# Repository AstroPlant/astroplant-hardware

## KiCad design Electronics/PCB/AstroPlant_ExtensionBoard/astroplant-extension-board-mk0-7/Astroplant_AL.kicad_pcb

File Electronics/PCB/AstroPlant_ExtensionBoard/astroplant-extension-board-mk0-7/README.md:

## Power supply configuration
You can select different configuration to supply the board, 
	On the 3.3V line: you can choose between power the board with the raspberry or with the onboard 3.3V generator
	On the 5V line you can choose to power the board through :
		Raspberry pi,
		Board 5V input,
		micro-USB
		
With the astroplant-kit you need 2 jumper :
		connect 3.3V with the onboard generator
		connect 5V to the Board 5V input,

## Boot-mode
To program the board you need the microcontroller to enter boot-mode, to do this power the board while pushing Boot button, or reset the board while pushing Boot button,
To leave Boot-mode, reset the board with the button, or switch the power Off and On without pushing on boot button

## Antenna 
Don't place R26 and C6 if you want to use the PCB antenna
or Don't place R25 to use the UFL connector with an antenna

## To manufacture the PCB you need these files:
  - gerber - track/component placement
  - .drl - drill placement 
  - .pos - component placement 
 These file are avaible in the /Outputs directory
 
The BOM is available in the main folder, as it is not part of the manufacturing files.

## If you want to generate new output files, follow these steps: 

First you'll need Kicad 7.0: https://www.kicad.org/download/ 
Then open the project by executing the .kicad_pro file, you will then be able to see the different elements of the project such as the schematic and the pcb,
If you want the gerber or drill map, open the pcb editor (.kicad_pcb) and go "File -> Fabrication output ->Gerbers/Drill/Component Placement/BOM".
For each file, select the output directory before generating

We'll use the general parameter for output files.
For Gerber, select layers: B_Cu,B_Mask,B_Paste,B_Silkscreen,F_Cu,F_Mask,F_Paste,F_Silkscreen,Edge_Cuts and User_Eco2
and leave the other options as they are.

Please note that if you have added new components, add an "MPN" (Manufacturer part number) field in the properties of 
these parts, which is the part identification number; this field will be used to generate the BOM. 

To generate the Bill of mateial (BOM) open the schematic editor 
and do: Tools -> Generate BOM and select bom_generator_astroplant in the folder bom, this is 
a python script that generates a BOM compatible with Eurocircuit.

Now that you have the output files you can have them manufactured and even have the components 
placed if you have the BOM, for example on Eurcocircuits.com

Here is a tutorial to do that : https://docs.google.com/document/d/1_ITujiSZbh2MQ0I3NJUg4zAOC5qoafzlOR5tIkIVDLY/edit?usp=sharing

# MK07

## Specs

* 5V Input
    * Power RPI
    * Power sensors actuators
* 24V Input
    * Mosfet Output
    * LEDs connector (not for the moment)
* 3x Buttons
    * GPIO5
    * GPIO6
    * GPIO7
* 2x 1-Wire lines (2 connectors)
    * GPIO17 Humidity
    * GPIO4 Water temp
* CO2 interface (Rx, Tx, 5V, GND)
* SPI interface (NRF24)
* I2C
    * 4x 3.3v
    * 2x 5V
* LEDs panel interface
    * GPIO21 Blue
    * GPIO20 Red
    * GPIO18 Far
* 3x mosfet output (5V or 24V) 2A
    * GPIO16 Fans
    * GPIO12 Pump
    * GPIO19 Spare
* Add LED
* Zigbee/Thread interface
* Analog to digital converter
	* 2x

GPIO13 is still not used

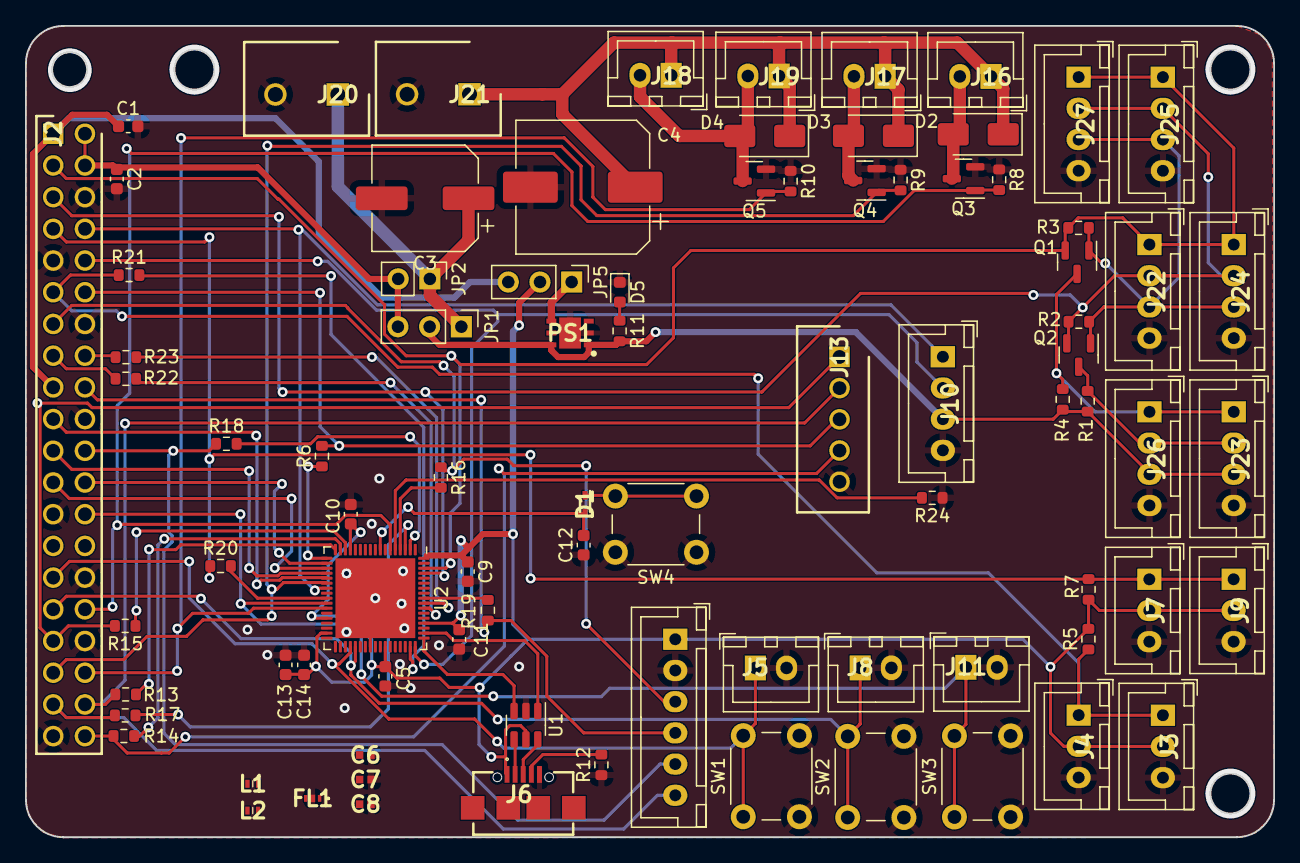
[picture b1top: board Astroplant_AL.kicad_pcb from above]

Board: 2 copper layers, 100.0 x 65.0 mm, 85 parts (0 on the bottom side), 64 nets.

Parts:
C1, C2, C5, C9, C10, C11, C12, C14: 100nF; C_0603_1608Metric
C3: 470uF; CP_Elec_8x6.9
C4: 470uF; CP_Elec_10x10.5
C6: GRM1555C1H1R2WA01D; CAPC1005X55N
C7: GRM1555C1HR30WA01D; CAPC1005X55N
C8: GRM1555C1HR80BA01D; CAPC1005X55N
C13: 100pF; C_0603_1608Metric
D1: BAT54KFILM; SODFL1608X70N
D2, D3, D4: S1A; D_SMA
D5: LED_Amber; LED_0603_1608Metric
FL1: LFB182G45CGFD436
J1: JST_XH_Relays; SHDR6W64P0X250_1X6_1740X575X700P
J2: 2x40 2.5mm Header; HDRV40W64P254X254_2X20_5080X508X869P
J3, J4, J7, J9: JST-XH_3; B3BXHALFSN
J5, J8, J11, J16, J17, J18, J19: JST_HX_2; SHDR2W64P0X250_1X2_740X575X700P
J6: 629105136821; MICRO-USB_2.0-SMT-TYPE-B_
J10: JST_XH_UART; B4BXHALFSN
J13: B5B-XH-A_LF__SN_; SHDR5W64P0X250_1X5_1490X575X700P
J20, J21: Conn_01x02; SHDR2W100P0X500_1X2_1000X750X990P
J22, J23, J24, J25, J26, J27: JST_XH_I2C; B4BXHALFSN
JP1, JP5: Jumper_3_Bridged12; PinHeader_1x03_P2.54mm_Vertical
JP2: Jumper_2_Bridged; PinHeader_1x02_P2.54mm_Vertical
L1: LQG15HS3N6S02D; LQG15WH0N7B02D
L2: LQG15HS2N7S02J; LQG15WH0N7B02D
PS1: LD39050PU33R; SON95P300X300X100-7N-D
Q1, Q2, Q3, Q4, Q5: IRLML6344TRPBF; SOT-23
R1, R2, R3, R4, R5, R7, R8, R9, R10, R12, R24: 10k; R_0603_1608Metric
R6, R13, R14, R15, R16, R17, R18, R19, R20, R21, R22, R23: 1k; R_0603_1608Metric
R11: 180; R_0603_1608Metric
SW1, SW2, SW3, SW4: SW_Push; SW_PUSH_6mm
U1: USBLC6-2SC6; SOT-23-6
U2: STM32WB55RGVx; QFN-68-1EP_8x8mm_P0.4mm_EP6.4x6.4mm

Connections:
3.3V_Generated: JP5.1 (A), PS1.4 (VOUT)
3.3V_RPi: C1.1, J2.1 (3V3), J2.17 (3V3), JP5.3 (B)
5V_IN: C3.1, J20.1, JP1.1 (A), JP2.1 (A)
5V_RPi: C2.1, J2.2 (5V), J2.4 (5V), JP1.3 (B), JP2.2 (B)
+3V3: C5.1, C9.1, C10.1, C11.1, C13.1, C14.1, J1.1 (DC+), J3.2 (PW), J4.2 (PW), J6.1, J7.2 (PW), J9.2 (PW), J22.3 (PW), J24.3 (PW), J25.3 (PW), J27.3 (PW), JP5.2 (C), Q1.1 (G), Q2.1 (G), R2.2, R3.2, R5.2, R7.2, U1.5 (VBUS), U2.14 (VDDA), U2.30 (VDD), U2.33 (VDDRF), U2.45 (VDD), U2.55 (VDDUSB), U2.68 (VDD)
+5V: J10.3 (PW), J23.3 (PW), J26.3 (PW), JP1.2 (C), PS1.1 (EN), PS1.6 (VIN), R1.2, R4.2, R11.2
+24V: C4.1, D2.1 (K), D3.1 (K), D4.1 (K), J16.1 (A), J17.1 (A), J18.1 (A), J19.1 (A), J21.1
CE0: J2.24 (~CE0/GPIO8), U2.19 (PA4)
GND: C1.2, C2.2, C3.2, C4.2, C5.2, C6.2, C7.2, C8.2, C9.2, C10.2, C11.2, C12.1, C13.2, C14.2, D5.1 (K), FL1.2 (GND), J1.2 (DC-), J2.6 (GND), J2.9 (GND), J2.14 (GND), J2.20 (GND), J2.25 (GND), J2.30 (GND), J2.34 (GND), J2.39 (GND), J3.3 (GND), J4.3 (GND), J5.2 (B), J6.5, J7.3 (GND), J8.2 (B), J9.3 (GND), J10.4 (GND), J11.2 (B), J13.5, J20.2, J21.2, J22.4 (GND), J23.4 (GND), J24.4 (GND), J25.4 (GND), J26.4 (GND), J27.4 (GND), PS1.2 (GND), PS1.7 (PAD), Q3.2 (S), Q4.2 (S), Q5.2 (S), R8.1, R9.1, R10.1, R12.1, R24.1, SW1.2, SW2.2, SW3.2, SW4.1, U1.2 (GND), U2.32 (VSSRF), U2.42 (VSSSMPS), U2.69 (VSS)
GPIO4: J2.7 (GCLK0/GPIO4), J7.1 (DATA), J9.1 (DATA), R7.1, R20.1
GPIO5: J2.29 (GCLK1/GPIO5), J5.1 (A), SW1.1, U2.38 (PB0)
GPIO6: J2.31 (GCLK2/GPIO6), J8.1 (A), SW2.1, U2.39 (PB1)
GPIO7: J2.26 (~CE1/GPIO7), J11.1 (A), SW3.1, U2.27 (PB2)
GPIO12: J2.32 (PWM0/GPIO12), Q3.1 (G), R8.2, U2.6 (PB8)
GPIO13: J2.33 (PWM1/GPIO13), J13.1, R15.2
GPIO16: J2.36 (GPIO16), Q5.1 (G), R10.2, U2.28 (PB10)
GPIO17: J2.11 (GPIO17), J3.1 (DATA), J4.1 (DATA), R5.1, R21.1
GPIO18: J2.12 (GPIO18/PWM0), J13.3, R6.2
GPIO19: J2.35 (GPIO19/MISO1), Q4.1 (G), R9.2, U2.23 (PA8)
GPIO20: J2.38 (GPIO20/MOSI1), J13.2, R13.2
GPIO21: J2.40 (GPIO21/SCLK1), J13.4, R14.2
GPIO22: J2.15 (GPIO22), R22.1
GPIO23: J2.16 (GPIO23), R23.1
GPIO24: J1.4 (CH2), J2.18 (GPIO24), R19.1
GPIO25: J1.5 (CH3), J2.22 (GPIO25), R18.1
GPIO26: J1.6 (CH4), J2.37 (GPIO26), R17.1
GPIO27: J1.3 (CH1), J2.13 (GPIO27), R16.1
MISO: J2.21 (MISO0/GPIO9), U2.21 (PA6)
MOSI: J2.19 (MOSI0/GPIO10), U2.22 (PA7)
unnamed: C6.1, L1.2
unnamed: D1.1, SW4.2
unnamed: D2.2 (A), J16.2 (B), Q3.3 (D)
unnamed: D3.2 (A), J17.2 (B), Q4.3 (D)
unnamed: D4.2 (A), J18.2 (B), J19.2 (B), Q5.3 (D)
unnamed: D5.2 (A), R11.1
unnamed: FL1.1 (IN), L1.1
unnamed: C7.1, FL1.3 (OUT), L2.2
unnamed: J6.2, U1.4 (I/O2)
unnamed: J6.3, U1.6 (I/O1)
unnamed: J6.4, R12.2
unnamed: C12.2, D1.2, U2.8 (NRST)
unnamed: R15.1, U2.15 (PA0)
unnamed: R14.1, U2.16 (PA1)
unnamed: R13.1, U2.17 (PA2)
unnamed: R6.1, U2.18 (PA3)
unnamed: U1.3 (I/O2), U2.52 (PA11)
unnamed: U1.1 (I/O1), U2.53 (PA12)
unnamed: R20.2, U2.26 (PC5)
unnamed: R21.2, U2.50 (PC6)
unnamed: R22.2, U2.58 (PC10)
unnamed: R23.2, U2.59 (PC11)
unnamed: R19.2, U2.60 (PC12)
unnamed: R18.2, U2.2 (PC13)
unnamed: R17.2, U2.3 (PC14)
unnamed: R16.2, U2.4 (PC15)
unnamed: R24.2, U2.5 (PH3)
unnamed: C8.1, L2.1, U2.31 (RF1)
RX: J2.10 (GPIO15/RXD), J10.2 (RX), U2.51 (PA10)
SCL: J2.5 (SCL/GPIO3), J22.2 (SCL), J24.2 (SCL), J25.2 (SCL), J27.2 (SCL), Q2.2 (S), R2.1, U2.65 (PB5)
SCLK: J2.23 (SCLK0/GPIO11), U2.20 (PA5)
SCL_5V: J23.2 (SCL), J26.2 (SCL), Q2.3 (D), R1.1
SDA: J2.3 (SDA/GPIO2), J22.1 (SDA), J24.1 (SDA), J25.1 (SDA), J27.1 (SDA), Q1.2 (S), R3.1, U2.66 (PB6)
SDA_5V: J23.1 (SDA), J26.1 (SDA), Q1.3 (D), R4.1
TX: J2.8 (GPIO14/TXD), J10.1 (TX), U2.24 (PA9)

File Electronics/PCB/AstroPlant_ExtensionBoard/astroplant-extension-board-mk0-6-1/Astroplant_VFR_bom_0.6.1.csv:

Source:,C:\Users\Aurel\Documents\Astroplant\Hardware\AstroPlant_VFR-master_v7.0\Project\Electronics\PCB\mk06\Astroplant_VFR.kicad_sch,,,,,,,,,,,
Date:,12/10/2023 15:22:05,,,,,,,,,,,
Tool:,Eeschema 7.0.7,,,,,,,,,,,
Generator:,C:\Program Files\KiCad\7.0\bin\scripting\plugins/bom_csv_grouped_by_value.py,,,,,,,,,,,
Component Count:,56,,,,,,,,,,,
,,,,,,,,,,,,
Collated Components:,,,,,,,,,,,,
,,,,,,,,,,,,
Item,Qty,Reference(s),Value,MPN (ref manufacturer),LibPart,Footprint,Datasheet,Digikey PN,Digikey Part Number,,Mouser Part Number,URL
1,2,"C1, C2",0.1uF,08055C104JAT2A ,Device:C_Small,Capacitor_SMD:C_0805_2012Metric,http://catalogs.avx.com/SurfaceMount.pdf,,478-3352-1-ND,,,https://www.digikey.com/product-detail/en/avx-corporation/08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
2,1,C3,470uF,875115150005,Astroplant_VFR-rescue:CP_Small-Device,Capacitor_SMD:CP_Elec_8x6.9,http://katalog.we-online.de/pbs/datasheet/875115150005.pdf,732-6443-1-ND,,,,
3,1,C4,470uF,EEH-ZK1E471P,Astroplant_VFR-rescue:CP-Device,Capacitor_SMD:CP_Elec_10x10.5,https://industrial.panasonic.com/cdbs/www-data/pdf/RDD0000/A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,P121398CT-ND,,,,
4,1,D1,LED_Blue,SMLEN3BC8TT86,Device:LED,LED_SMD:LED_0603_1608Metric,https://fscdn.rohm.com/en/products/databook/datasheet/opto/l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,,,, 755-SMLEN3BC8TT86 ,
5,3,"D2, D3, D4",S1A,S1A-13-F,Astroplant_VFR-rescue:D_ALT-Device,Diode_SMD:D_SMA,https://www.fairchildsemi.com/datasheets/S1/S1A.pdf,,S1AFSCT-ND,,,https://www.digikey.com/product-detail/en/on-semiconductor/S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
6,1,D5,LED_Amber,SML-D12D8WT8,Device:LED,LED_SMD:LED_0603_1608Metric,https://fscdn.rohm.com/en/products/databook/datasheet/opto/l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,,,, 755-SML-D12D8WT86C,
7,1,J1,JST_XH_Relays,B6B-XH-A(LF)(SN),Astroplant_VFR-rescue:JST_XH_Relays-JST_connector,Connector_JST:JST_XH_B06B-XH-A_1x06_P2.50mm_Vertical,http://www.jst-mfg.com/product/pdf/eng/eXH.pdf,,455-2271-ND,,,https://www.digikey.com/products/en?keywords=B6B-XH-A(LF)(SN)%20
8,1,J2,2x40 2.5mm Header,61304021121,Connector:Raspberry_Pi_2_3,footprints:Pin_Header_Straight_2x20_Pitch2.54mm,http://katalog.we-online.de/em/datasheet/6130xx21121.pdf,,732-5310-ND,,,https://www.digikey.com/product-detail/en/wurth-electronics-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
9,4,"J3, J4, J7, J9",JST-XH_3,B3B-XH-A(LF)(SN) ,Astroplant_VFR-rescue:JST-XH_3-JST_connector,Connector_JST:JST_XH_B03B-XH-A_1x03_P2.50mm_Vertical,http://www.jst-mfg.com/product/pdf/eng/eXH.pdf,,455-2248-ND,,,https://www.digikey.com/products/en?keywords=B3B-XH-A(LF)(SN)%20
10,7,"J5, J8, J11, J16, J17, J18, J19",JST_HX_2,B2B-XH-A(LF)(SN) ,Astroplant_VFR-rescue:JST_HX_2-JST_connector,Connector_JST:JST_XH_B02B-XH-A_1x02_P2.50mm_Vertical,http://www.jst-mfg.com/product/pdf/eng/eXH.pdf,,455-2247-ND,,,https://www.digikey.com/products/en?keywords=%20B2B-XH-A(LF)(SN)%20
11,1,J6,Conn_02x04_Odd_Even,X,Connector_Generic:Conn_02x04_Odd_Even,footprints:Pin_Header_Straight_2x04_Pitch2.54mm,~,,,,,
12,1,J10,JST_XH_UART,B4B-XH-A(LF)(SN),Astroplant_VFR-rescue:JST_XH_UART-JST_connector,Connector_JST:JST_XH_B04B-XH-A_1x04_P2.50mm_Vertical,http://www.jst-mfg.com/product/pdf/eng/eXH.pdf,,455-2249-ND,,,https://www.digikey.com/products/en?mpart=B4B-XH-A%28LF%29%2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
13,1,J12,JST-XH_LED_GND,B4B-XH-A(LF)(SN),Astroplant_VFR-rescue:JST-XH_LED_GND-JST_connector,Connector_JST:JST_XH_B04B-XH-A_1x04_P2.50mm_Vertical,,,455-2249-ND,,,
14,2,"J20, J21",Conn_01x02,691102710002,Connector:Screw_Terminal_01x02,footprints:TerminalBlock_bornier-2_P5.08mm,https://www.we-online.com/components/products/datasheet/6911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,,710-691102710002,, 710-691102710002,https://www.we-online.com/components/products/datasheet/6911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
15,6,"J22, J23, J24, J25, J26, J27",JST_XH_I2C,B4B-XH-A(LF)(SN) ,Astroplant_VFR-rescue:JST_XH_I2C-Astroplant_VFR-rescue-Astroplant_VFR-rescue,Connector_JST:JST_XH_B04B-XH-A_1x04_P2.50mm_Vertical,http://www.jst-mfg.com/product/pdf/eng/eXH.pdf,,455-2249-ND,,,https://www.digikey.com/products/en?keywords=B4B-XH-A(LF)(SN)%20
16,1,JP1,Jumper_3_Bridged12,61300311121,Astroplant_VFR-rescue:Jumper_3_Bridged12-Jumper,Connector_PinHeader_2.54mm:PinHeader_1x03_P2.54mm_Vertical,http://katalog.we-online.de/em/datasheet/6130xx11121.pdf,732-5316-ND,,,,
17,1,JP2,Jumper_2_Bridged,61300211121,Jumper:Jumper_2_Bridged,Connector_PinHeader_2.54mm:PinHeader_1x02_P2.54mm_Vertical,http://katalog.we-online.de/em/datasheet/6130xx11121.pdf,732-5315-ND,,,,
18,2,"JP3, JP4",Jumper_2_Bridged,60900213421,Jumper:Jumper_2_Bridged,,https://www.we-online.com/components/products/datasheet/6090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,,,,,
19,5,"Q1, Q2, Q3, Q4, Q5",IRLML6344TRPBF,IRLML6344TRPBF,Astroplant_VFR-rescue:IRLML6344-AstroPlant,Package_TO_SOT_SMD:SOT-23,https://www.infineon.com/dgdl/irlml6344pbf.pdf?fileId=5546d4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,,IRLML6344TRPBFCT-ND,,,https://www.digikey.com/product-detail/en/infineon-technolog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
20,6,"R1, R2, R3, R4, R5, R7",10K,RC0805FR-0710KL,Device:R_Small,Resistor_SMD:R_0805_2012Metric,http://www.yageo.com/documents/recent/PYu-RC_Group_51_RoHS_L_8.pdf,311-10.0KCRCT-ND,311-10.0KCRCT-ND,,,https://www.digikey.com/product-detail/en/yageo/RC0805FR-071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
21,1,R6,27,RR0816Q-270-D,Device:R_Small,Resistor_SMD:R_0603_1608Metric,http://www.susumu.co.jp/common/pdf/n_catalog_partition05_en.pdf,RR08Q27DCT-ND,,,,
22,3,"R8, R9, R10",100K,RC0805FR-07100KL ,Device:R,Resistor_SMD:R_0805_2012Metric,http://www.yageo.com/documents/recent/PYu-RC_Group_51_RoHS_L_8.pdf,,311-100KCRCT-ND,,,https://www.digikey.com/product-detail/en/yageo/RC0805FR-071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
23,1,R11,180,ESR10EZPJ181,Device:R_Small,Resistor_SMD:R_0805_2012Metric,http://www.rohm.com/web/global/datasheet/ESR01MZPF/esr-e,RHM180KCT-ND,,,,
24,3,"SW1, SW2, SW3",SW_Push,430156043726,Astroplant_VFR-rescue:SW_Push-Astroplant_VFR-rescue-Astroplant_VFR-rescue,Button_Switch_THT:SW_PUSH_6mm,https://www.we-online.com/components/products/datasheet/4301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,,,, 710-430156043726 ,https://nl.mouser.com/ProductDetail/Wurth-Elektronik/4301560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

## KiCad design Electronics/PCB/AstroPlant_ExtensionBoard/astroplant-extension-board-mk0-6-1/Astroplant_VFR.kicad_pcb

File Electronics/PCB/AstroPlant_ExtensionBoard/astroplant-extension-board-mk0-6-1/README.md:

## To manufacture the PCB you need these files:
  - gerber - track/component placement
  - .drl - drill placement 
  - .pos - component placement 
 These file are avaible in the /Outputs directory
 
The BOM is available in the main folder, as it is not part of the manufacturing files.

## If you want to generate new output files, follow these steps: 

First you'll need Kicad 7.0: https://www.kicad.org/download/ 
Then open the project by executing the .kicad_pro file, you will then be able to see the different elements of the project such as the schematic and the pcb,
If you want the gerber or drill map, open the pcb editor (.kicad_pcb) and go "File -> Fabrication output ->Gerbers/Drill/Component Placement/BOM".
For each file, select the output directory before generating

We'll use the general parameter for output files.
For Gerber, select layers: B_Cu,B_Mask,B_Paste,B_Silkscreen,F_Cu,F_Mask,F_Paste,F_Silkscreen,Edge_Cuts and User_Eco2
and leave the other options as they are.
 
## MK06.1

## Specs

* 5V Input
    * Power RPI
    * Power sensors actuators
* 24V Input
    * Mosfet Output
    * LEDs connector (not for the moment)
* 3x Buttons
    * GPIO5
    * GPIO6
    * GPIO7
* 2x 1-Wire lines (2 connectors)
    * GPIO17 Humidity
    * GPIO4 Water temp
* CO2 interface (Rx, Tx, 5V, GND)
* SPI interface (NRF24)
* I2C
    * 4x 3.3v
    * 2x 5V
* LEDs panel interface
    * GPIO21 Blue
    * GPIO20 Red
    * GPIO18 Far
* 3x mosfet output (5V or 24V) 2A
    * GPIO16 Fans
    * GPIO12 Pump
    * GPIO19 Spare
* Add LED

GPIO13 is still not used

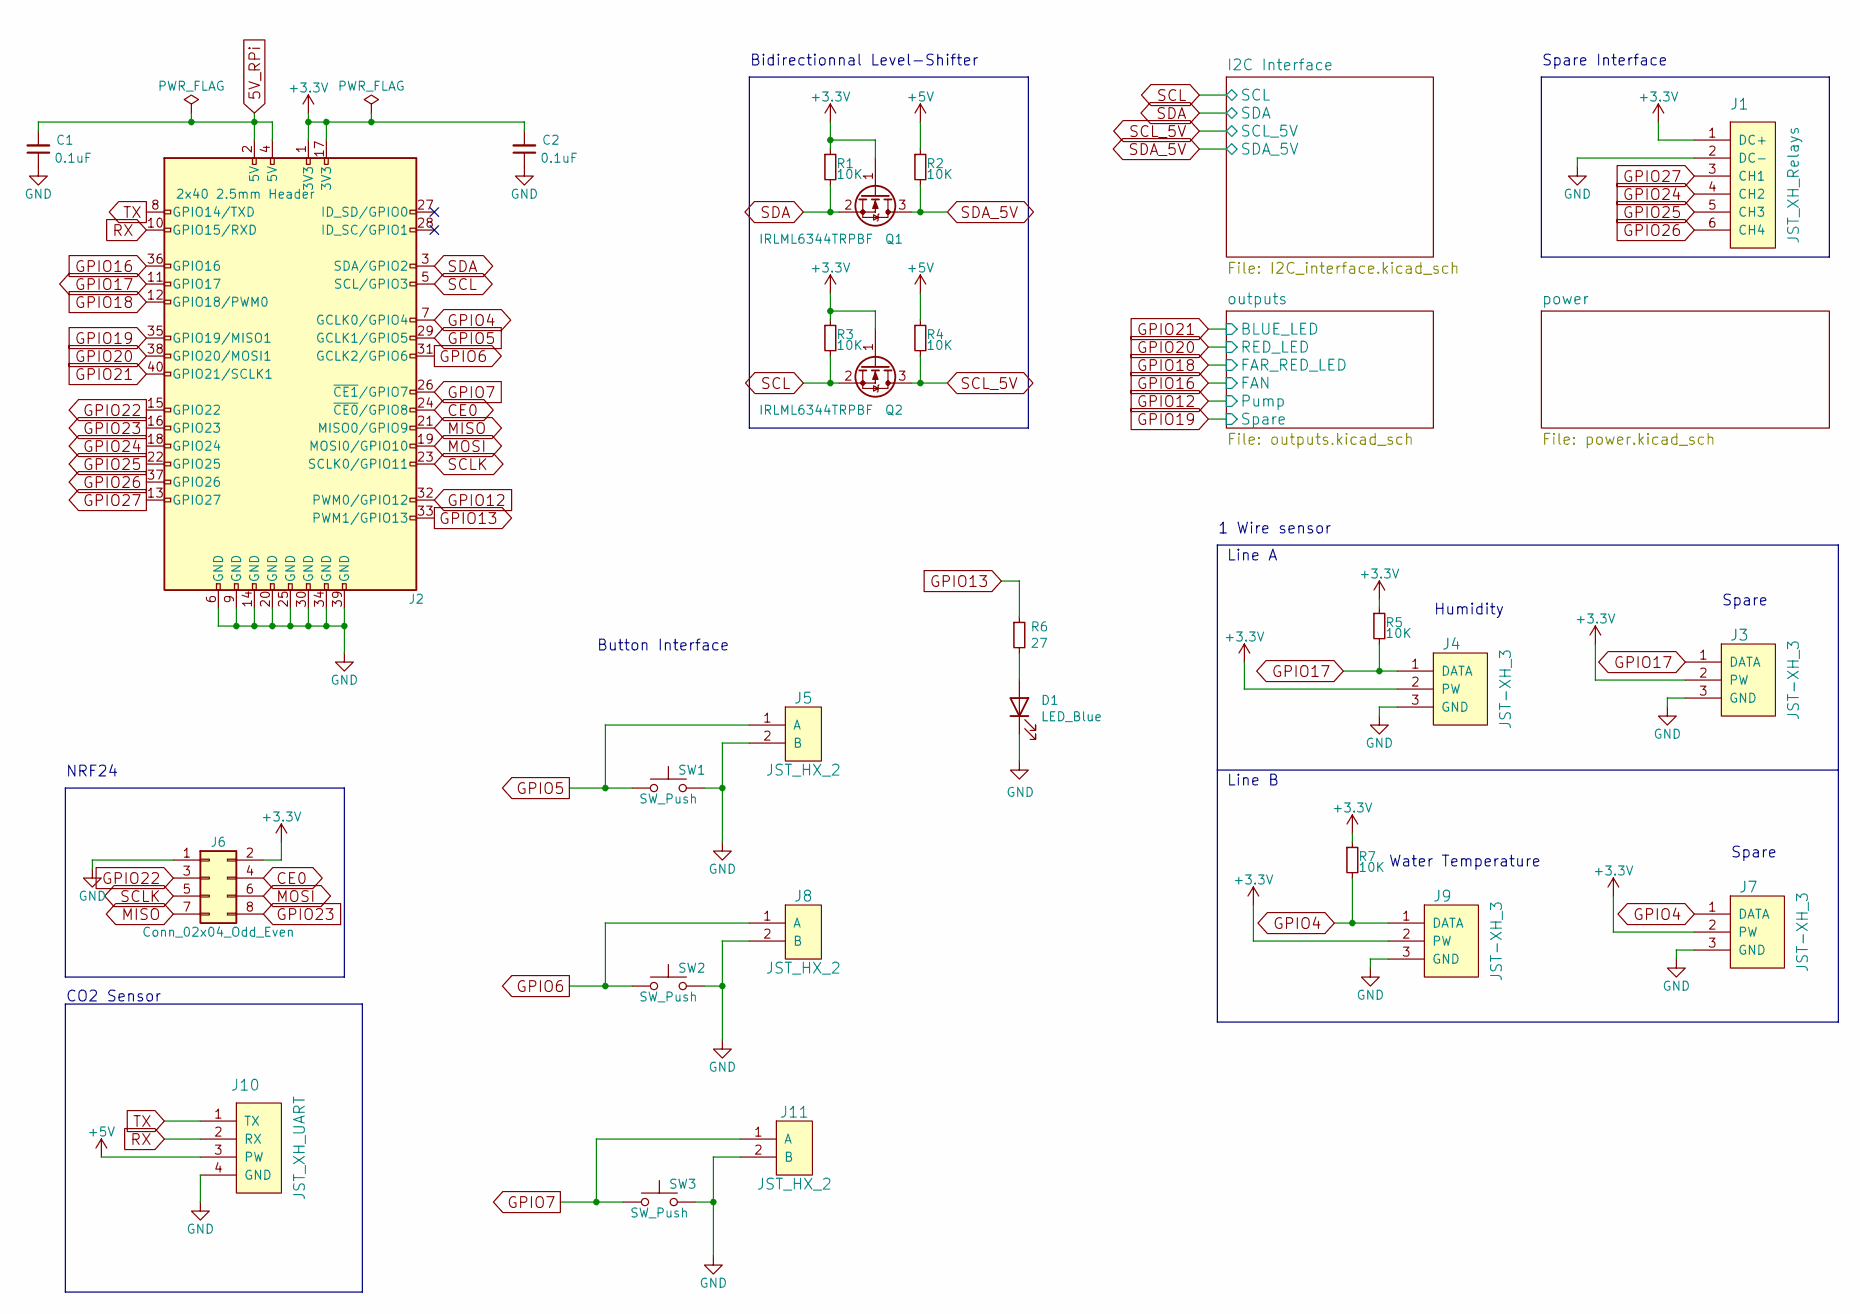
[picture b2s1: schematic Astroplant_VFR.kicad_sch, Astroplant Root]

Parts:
C1, C2: 0.1uF; C_0805_2012Metric; MPN 08055C104JAT2A; Digikey Part Number 478-3352-1-ND
D1: LED_Blue; LED_0603_1608Metric; MPN SMLEN3BC8TT86; Mouser PN 755-SMLEN3BC8TT86
J1: JST_XH_Relays; JST_XH_B06B-XH-A_1x06_P2.50mm_Vertical; MPN B6B-XH-A(LF)(SN); Digikey Part Number 455-2271-ND
J2: 2x40 2.5mm Header; Pin_Header_Straight_2x20_Pitch2.54mm; MPN 61304021121; Digikey Part Number 732-5310-ND
J3, J4, J7, J9: JST-XH_3; JST_XH_B03B-XH-A_1x03_P2.50mm_Vertical; MPN B3B-XH-A(LF)(SN); Digikey Part Number 455-2248-ND
J5, J8, J11: JST_HX_2; JST_XH_B02B-XH-A_1x02_P2.50mm_Vertical; MPN B2B-XH-A(LF)(SN); Digikey Part Number 455-2247-ND
J6: Conn_02x04_Odd_Even; Pin_Header_Straight_2x04_Pitch2.54mm
J10: JST_XH_UART; JST_XH_B04B-XH-A_1x04_P2.50mm_Vertical; MPN B4B-XH-A(LF)(SN); Digikey Part Number 455-2249-ND
Q1, Q2: IRLML6344TRPBF; SOT-23; MPN IRLML6344TRPBF; Digikey Part Number IRLML6344TRPBFCT-ND
R1, R2, R3, R4: 10K; R_0805_2012Metric; MPN RC0805FR-0710KL; Digikey PN 311-10.0KCRCT-ND
R5, R7: 10K; R_0805_2012Metric; MPN RC0805FR-0710KL; Digikey Part Number 311-10.0KCRCT-ND
R6: 27; R_0603_1608Metric; MPN RR0816Q-270-D; Digikey PN RR08Q27DCT-ND
SW1, SW2, SW3: SW_Push; SW_PUSH_6mm; MPN 430156043726; Mouser Part Number 710-430156043726

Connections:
5V_RPi: C1.2, J2.2 (5V), J2.4 (5V); also elsewhere on the board
+3V3: C2.2, J1.1 (DC+), J2.1 (3V3), J2.17 (3V3), J3.2 (PW), J4.2 (PW), J6.2, J7.2 (PW), J9.2 (PW), Q1.1 (G), Q2.1 (G), R1.1, R3.1, R5.1, R7.1; also elsewhere on the board
+5V: J10.3 (PW), R2.1, R4.1; also elsewhere on the board
CE0: J2.24 (~CE0/GPIO8), J6.4
GND: C1.1, C2.1, D1.1 (K), J1.2 (DC-), J2.6 (GND), J2.9 (GND), J2.14 (GND), J2.20 (GND), J2.25 (GND), J2.30 (GND), J2.34 (GND), J2.39 (GND), J3.3 (GND), J4.3 (GND), J5.2 (B), J6.1, J7.3 (GND), J8.2 (B), J9.3 (GND), J10.4 (GND), J11.2 (B), SW1.2, SW2.2, SW3.2; also elsewhere on the board
GPIO4: J2.7 (GCLK0/GPIO4), J7.1 (DATA), J9.1 (DATA), R7.2
GPIO5: J2.29 (GCLK1/GPIO5), J5.1 (A), SW1.1
GPIO6: J2.31 (GCLK2/GPIO6), J8.1 (A), SW2.1
GPIO7: J2.26 (~CE1/GPIO7), J11.1 (A), SW3.1
GPIO12: J2.32 (PWM0/GPIO12); also elsewhere on the board
GPIO13: J2.33 (PWM1/GPIO13), R6.1
GPIO16: J2.36 (GPIO16); also elsewhere on the board
GPIO17: J2.11 (GPIO17), J3.1 (DATA), J4.1 (DATA), R5.2
GPIO18: J2.12 (GPIO18/PWM0); also elsewhere on the board
GPIO19: J2.35 (GPIO19/MISO1); also elsewhere on the board
GPIO20: J2.38 (GPIO20/MOSI1); also elsewhere on the board
GPIO21: J2.40 (GPIO21/SCLK1); also elsewhere on the board
GPIO22: J2.15 (GPIO22), J6.3
GPIO23: J2.16 (GPIO23), J6.8
GPIO24: J1.4 (CH2), J2.18 (GPIO24)
GPIO25: J1.5 (CH3), J2.22 (GPIO25)
GPIO26: J1.6 (CH4), J2.37 (GPIO26)
GPIO27: J1.3 (CH1), J2.13 (GPIO27)
MISO: J2.21 (MISO0/GPIO9), J6.7
MOSI: J2.19 (MOSI0/GPIO10), J6.6
unnamed: D1.2 (A), R6.2
RX: J2.10 (GPIO15/RXD), J10.2 (RX)
SCL: J2.5 (SCL/GPIO3), Q2.2 (S), R3.2; also elsewhere on the board
SCLK: J2.23 (SCLK0/GPIO11), J6.5
SCL_5V: Q2.3 (D), R4.2; also elsewhere on the board
SDA: J2.3 (SDA/GPIO2), Q1.2 (S), R1.2; also elsewhere on the board
SDA_5V: Q1.3 (D), R2.2; also elsewhere on the board
TX: J2.8 (GPIO14/TXD), J10.1 (TX)

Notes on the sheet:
NRF24
Button Interface
Bidirectionnal Level-Shifter
Humidity
1 Wire sensor
Spare Interface
Line B
CO2 Sensor
Water Temperature
Spare
Line A

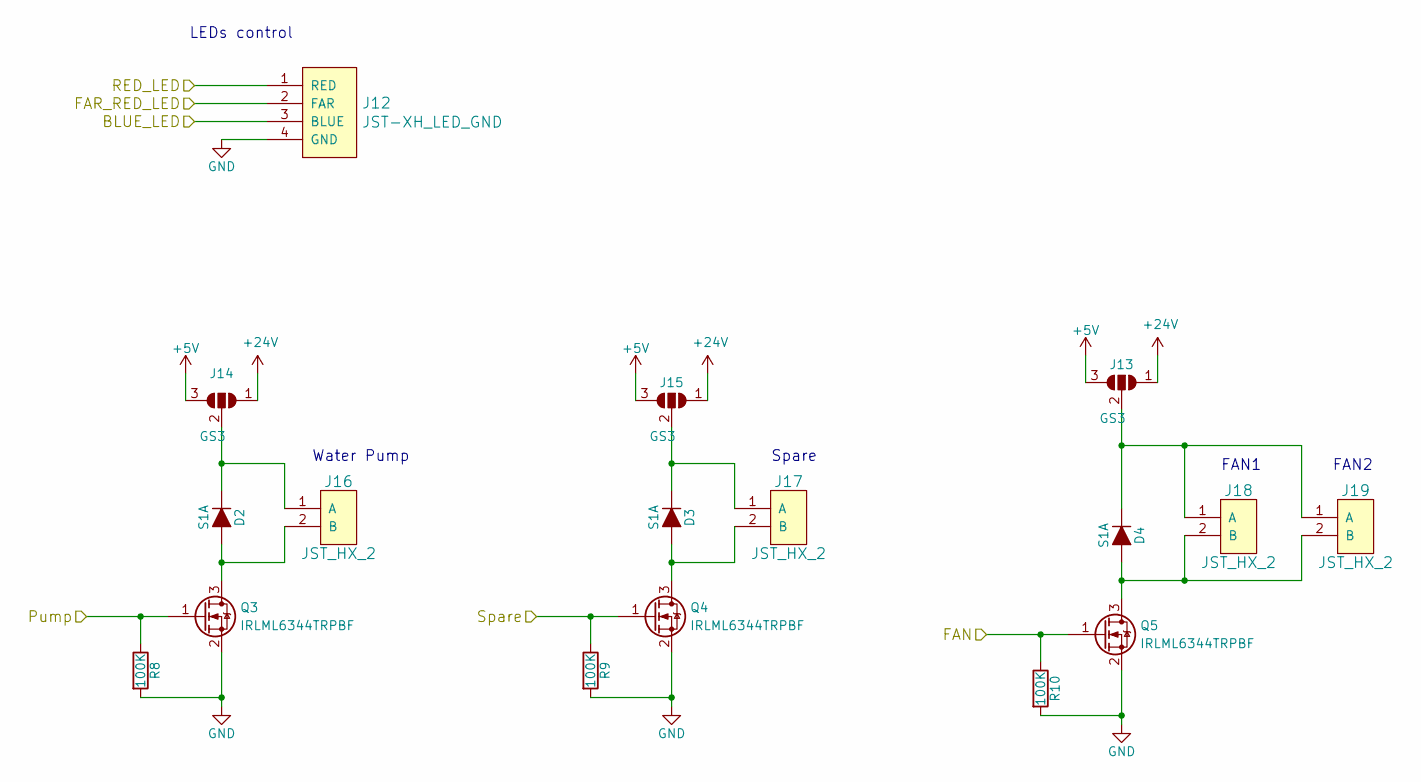
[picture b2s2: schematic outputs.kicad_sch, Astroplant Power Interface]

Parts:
D2, D3, D4: S1A; D_SMA; MPN S1A-13-F; Digikey Part Number S1AFSCT-ND
J12: JST-XH_LED_GND; JST_XH_B04B-XH-A_1x04_P2.50mm_Vertical
J13, J14, J15: GS3; SolderJumper-3_P2.0mm_Open_TrianglePad1.0x1.5mm
J16, J17, J18, J19: JST_HX_2; JST_XH_B02B-XH-A_1x02_P2.50mm_Vertical; MPN B2B-XH-A(LF)(SN); Digikey Part Number 455-2247-ND
Q3, Q4, Q5: IRLML6344TRPBF; SOT-23; MPN IRLML6344TRPBF; Digikey Part Number IRLML6344TRPBFCT-ND
R8, R9, R10: 100K; R_0805_2012Metric; MPN RC0805FR-07100KL; Digikey Part Number 311-100KCRCT-ND

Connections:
+5V: J13.3 (B), J14.3 (B), J15.3 (B); also elsewhere on the board
+24V: J13.1 (A), J14.1 (A), J15.1 (A); also elsewhere on the board
GND: J12.4 (GND), Q3.2 (S), Q4.2 (S), Q5.2 (S), R8.2, R9.2, R10.2; also elsewhere on the board
GPIO12: Q3.1 (G), R8.1; also elsewhere on the board
GPIO16: Q5.1 (G), R10.1; also elsewhere on the board
GPIO18: J12.2 (FAR); also elsewhere on the board
GPIO19: Q4.1 (G), R9.1; also elsewhere on the board
GPIO20: J12.1 (RED); also elsewhere on the board
GPIO21: J12.3 (BLUE); also elsewhere on the board
unnamed: D2.2 (A), J16.2 (B), Q3.3 (D)
unnamed: D2.1 (K), J14.2 (C), J16.1 (A)
unnamed: D3.2 (A), J17.2 (B), Q4.3 (D)
unnamed: D3.1 (K), J15.2 (C), J17.1 (A)
unnamed: D4.2 (A), J18.2 (B), J19.2 (B), Q5.3 (D)
unnamed: D4.1 (K), J13.2 (C), J18.1 (A), J19.1 (A)

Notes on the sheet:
Spare
LEDs control
Water Pump
FAN2
FAN1

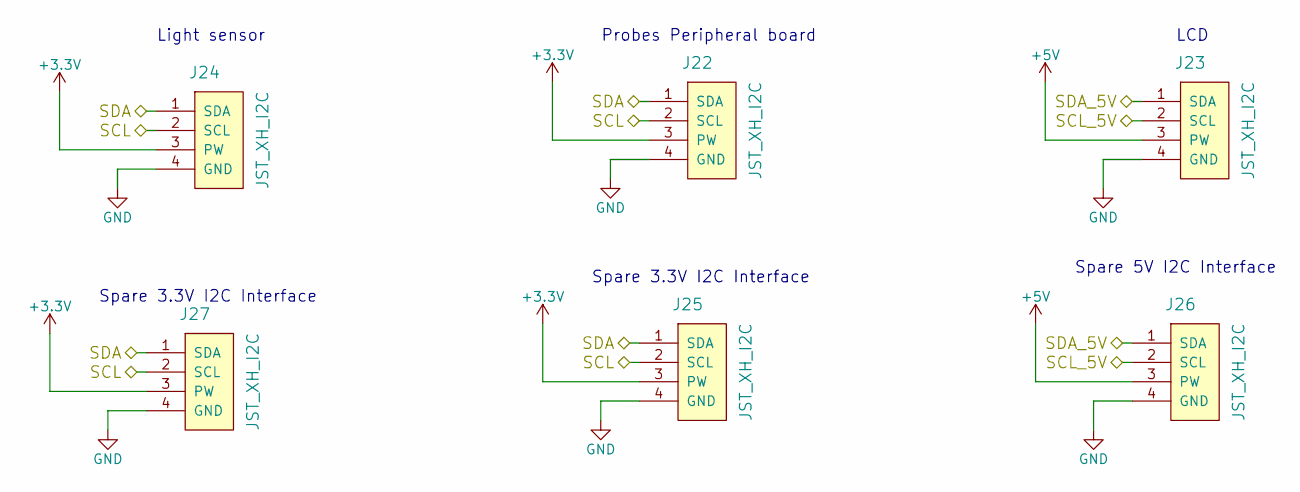
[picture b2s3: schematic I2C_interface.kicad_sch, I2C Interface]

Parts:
J22, J23, J24, J25, J26, J27: JST_XH_I2C; JST_XH_B04B-XH-A_1x04_P2.50mm_Vertical; MPN B4B-XH-A(LF)(SN); Digikey Part Number 455-2249-ND

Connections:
+3V3: J22.3 (PW), J24.3 (PW), J25.3 (PW), J27.3 (PW); also elsewhere on the board
+5V: J23.3 (PW), J26.3 (PW); also elsewhere on the board
GND: J22.4 (GND), J23.4 (GND), J24.4 (GND), J25.4 (GND), J26.4 (GND), J27.4 (GND); also elsewhere on the board
SCL: J22.2 (SCL), J24.2 (SCL), J25.2 (SCL), J27.2 (SCL); also elsewhere on the board
SCL_5V: J23.2 (SCL), J26.2 (SCL); also elsewhere on the board
SDA: J22.1 (SDA), J24.1 (SDA), J25.1 (SDA), J27.1 (SDA); also elsewhere on the board
SDA_5V: J23.1 (SDA), J26.1 (SDA); also elsewhere on the board

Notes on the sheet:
Spare 5V I2C Interface
Light sensor
LCD
Spare 3.3V I2C Interface
Probes Peripheral board

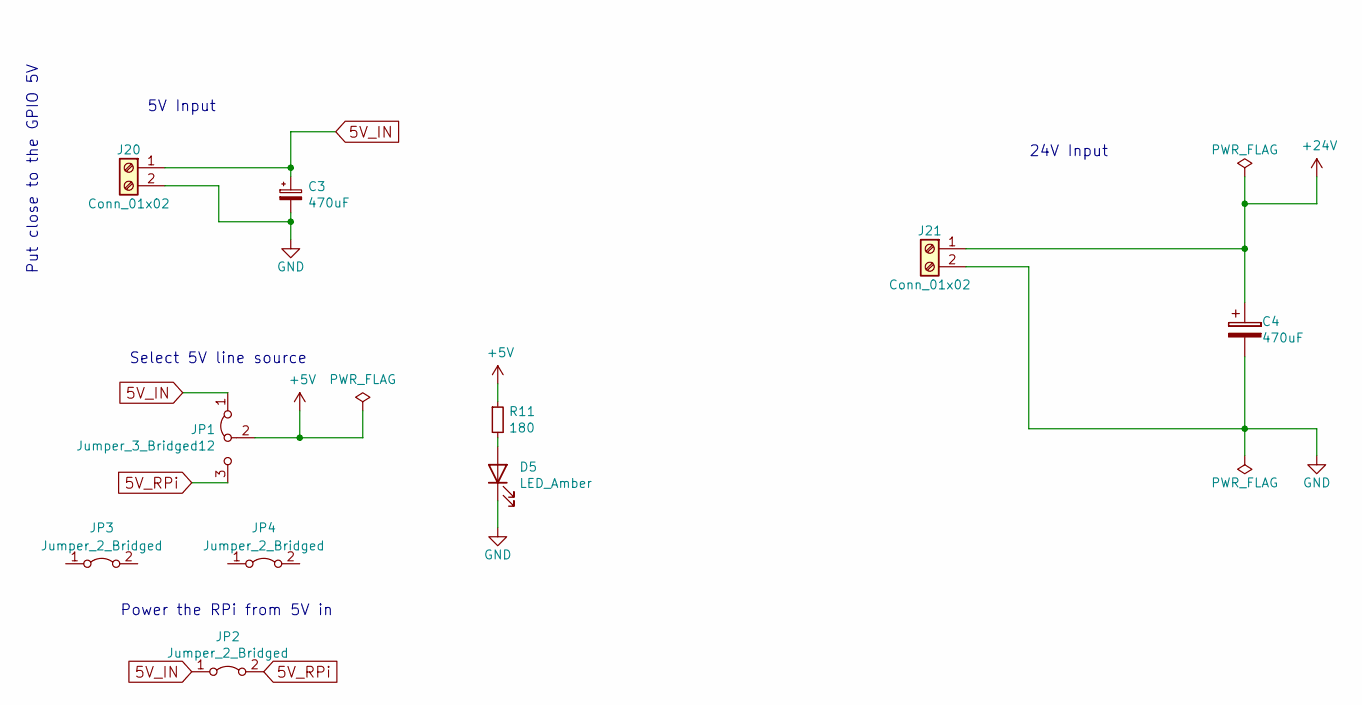
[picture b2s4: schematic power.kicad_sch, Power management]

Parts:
C3: 470uF; CP_Elec_8x6.9; MPN 875115150005; Digikey PN 732-6443-1-ND
C4: 470uF; CP_Elec_10x10.5; MPN EEH-ZK1E471P; Digikey PN P121398CT-ND
D5: LED_Amber; LED_0603_1608Metric; MPN SML-D12D8WT8; Mouser PN 755-SML-D12D8WT86C
J20: Conn_01x02; TerminalBlock_bornier-2_P5.08mm; MPN 691102710002; Digikey Part Number 710-691102710002
J21: Conn_01x02; TerminalBlock_bornier-2_P5.08mm; MPN 691102710002; Mouser Part Number 710-691102710002
JP1: Jumper_3_Bridged12; PinHeader_1x03_P2.54mm_Vertical; MPN 61300311121; Digikey PN 732-5316-ND
JP2: Jumper_2_Bridged; PinHeader_1x02_P2.54mm_Vertical; MPN 61300211121; Digikey PN 732-5315-ND
JP3, JP4: Jumper_2_Bridged; MPN 60900213421
R11: 180; R_0805_2012Metric; MPN ESR10EZPJ181; Digikey PN RHM180KCT-ND

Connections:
5V_IN: C3.1, J20.1, JP1.1 (A), JP2.1 (A)
5V_RPi: JP1.3 (B), JP2.2 (B); also elsewhere on the board
+5V: JP1.2 (C), R11.1; also elsewhere on the board
+24V: C4.1, J21.1; also elsewhere on the board
GND: C3.2, C4.2, D5.1 (K), J20.2, J21.2; also elsewhere on the board
unnamed: D5.2 (A), R11.2

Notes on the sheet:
24V Input
Select 5V line source
5V Input
Power the RPi from 5V in
Put close to the GPIO 5V

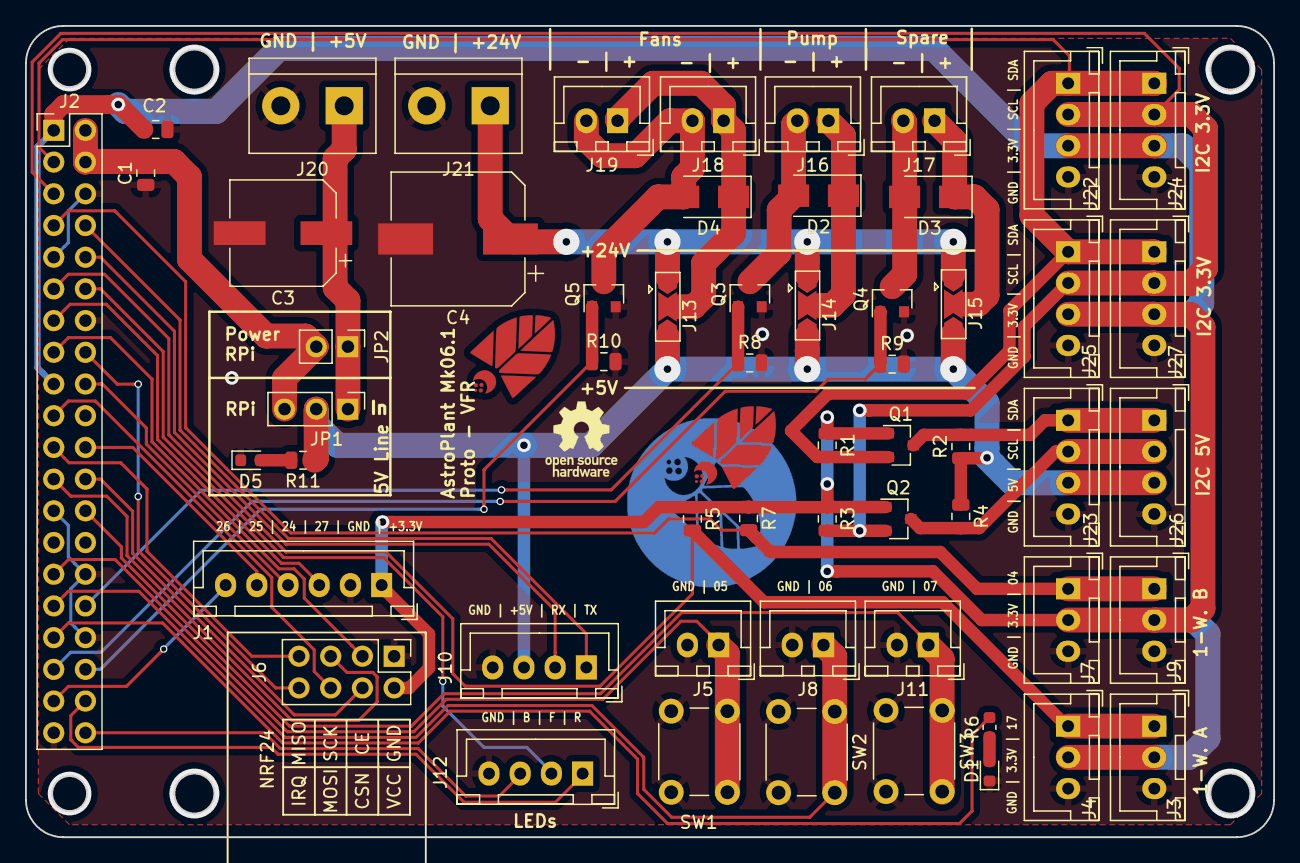
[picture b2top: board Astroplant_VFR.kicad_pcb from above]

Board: 2 copper layers, 100.0 x 65.0 mm, 57 parts (0 on the bottom side), 42 nets.

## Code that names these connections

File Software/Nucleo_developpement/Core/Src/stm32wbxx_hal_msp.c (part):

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
    __HAL_RCC_GPIOB_CLK_ENABLE();
    /**I2C1 GPIO Configuration
    PB8     ------> I2C1_SCL
    PB9     ------> I2C1_SDA
    */
    GPIO_InitStruct.Pin = GPIO_PIN_8|GPIO_PIN_9;
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    __HAL_RCC_I2C1_CLK_DISABLE();

    /**I2C1 GPIO Configuration
    PB8     ------> I2C1_SCL
    PB9     ------> I2C1_SDA
    */
    HAL_GPIO_DeInit(GPIOB, GPIO_PIN_8);
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
    __HAL_RCC_GPIOA_CLK_ENABLE();
    /**SPI1 GPIO Configuration
    PA5     ------> SPI1_SCK
    PA6     ------> SPI1_MISO
    PA7     ------> SPI1_MOSI
    */
    GPIO_InitStruct.Pin = GPIO_PIN_5|GPIO_PIN_6;
    GPIO_InitStruct.Mode = GPIO_MODE_AF_PP;
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    __HAL_RCC_SPI1_CLK_DISABLE();

    /**SPI1 GPIO Configuration
    PA1     ------> SPI1_SCK
    PA6     ------> SPI1_MISO
    PA7     ------> SPI1_MOSI
    */
    HAL_GPIO_DeInit(GPIOA, GPIO_PIN_1|GPIO_PIN_6|GPIO_PIN_7);

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
    __HAL_RCC_GPIOB_CLK_ENABLE();
    /**USART1 GPIO Configuration
    PB6     ------> USART1_TX
    PB7     ------> USART1_RX
    */
    GPIO_InitStruct.Pin = STLINK_RX_Pin|STLINK_TX_Pin;
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    __HAL_RCC_USART1_CLK_DISABLE();

    /**USART1 GPIO Configuration
    PB6     ------> USART1_TX
    PB7     ------> USART1_RX
    */
    HAL_GPIO_DeInit(GPIOB, STLINK_RX_Pin|STLINK_TX_Pin);
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
    __HAL_RCC_GPIOA_CLK_ENABLE();
    /**USB GPIO Configuration
    PA11     ------> USB_DM
    PA12     ------> USB_DP
    */
    GPIO_InitStruct.Pin = GPIO_PIN_11|GPIO_PIN_12;
    GPIO_InitStruct.Mode = GPIO_MODE_AF_PP;
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    __HAL_RCC_USB_CLK_DISABLE();

    /**USB GPIO Configuration
    PA11     ------> USB_DM
    PA12     ------> USB_DP
    */
    HAL_GPIO_DeInit(GPIOA, GPIO_PIN_11|GPIO_PIN_12);

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
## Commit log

2018-09-11 Add Electronics README
2018-09-11 Documentation title on Electronics README
2018-09-21 add extension board mk06 as submodule
2018-09-21 add extension board mk05 as submodule
2018-09-21 add extension LEDs mk0.1-2 as submodule
2018-10-08 Add production files for leds and mk0 extension board
2018-10-12 add power wiring svg schematics
2018-11-13 license
2018-11-13 update license
2018-11-13 remove old license
2018-11-13 change name
2018-11-13 removed old name
2018-11-16 update submodules
2018-11-19 Extension Mk06 add gerber bottom mask
2018-11-27 add position to extension Mk06 and leds
2018-12-09 update wiring schematics
2023-10-18 Add new mk0.6.1 version (component replacement)
2023-10-20 Remove obselete files
2023-10-20 improved readme + deletion of other unnecessary files
2023-10-25 Readme and gitignore modification
2023-11-02 First commit of MK07
2023-11-09 First commit of the software
    An example code of a SPI communication between a Raspberry and stm32 programs to send and receive a "Hello"
2023-11-17 change .gitinore
2023-11-17 Update schematic and change library path
2023-11-22 Update fp_lib_table
    Update fp_lib_table to solve library issues
2023-11-22 Convert all absolute paths to relative ones with forward slashes
2023-11-22 Place components on PCB
2023-11-22 Fix remaining absolute paths
2023-11-24 Add route to PCB
    Not the final version of the PCB, missing components for the antenna and also non-component things like the astroplant logo, the version and placement of the component designators.
2023-11-26 Fix accidentally committed conflicts
2023-11-29 Completed version of the project
    Generate outputs (BOM, Drill, Pkp, Gerber)
    Added connectors descritption (like "I2C 3.3V" dor the corresponding connector)
    Added a connector to an external antenna
    Changed routing
    Changed component placement
    Added a script to generate a usable BOM
2023-11-29 Changed USB connector's pad, and updatded gerbers
2023-11-29 Added text to give information about the jumper connector and updated gerber
2023-11-29 Solved processing notes from aisler by changing micro usb connector
2023-11-30 Changed PCB, add a LED to simplify tests
2023-11-30 Fix paths to relative
2023-12-07 Updated PCB from a backup save to solve issue with git
2023-12-22 Last commit (software + hardware change)
    hardware : updated readme, change pcb to solve the issues of the 1st prototype
    software : add code (to create a zigbee network)
2024-03-22 Updated PCB from a backup save, solve issues of the 1st prototype
2024-03-22 Add test software
    - An example code of a SPI communication between a Raspberry and stm32 programs to send and receive a "Hello"
2024-03-22 Create a Zigbee network
2024-05-12 Fix the antenna (Implies a change in PCB routing)+ improve readme (add a tutorial to make the board on eurocicruit).

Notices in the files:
Software/Nucleo_developpement/Core/Src/stm32wbxx_hal_msp.c:
Copyright (c) 2023 STMicroelectronics.
All rights reserved.
This software is licensed under terms that can be found in the LICENSE file
